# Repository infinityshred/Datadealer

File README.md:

# Datadealer
Datadealer synthesizer
Datadealer is a clone of Olivier Gillet's Shruthi-1 (https://github.com/pichenettes/shruthi-1). All boards in this repository are released under a cc-by-sa 3.0 license.

The firmware is released under a GPL3.0 license. It includes a
reimplementation of the formant synthesis algorithm used in Peter Knight's
Cantarino speech synthesizer.

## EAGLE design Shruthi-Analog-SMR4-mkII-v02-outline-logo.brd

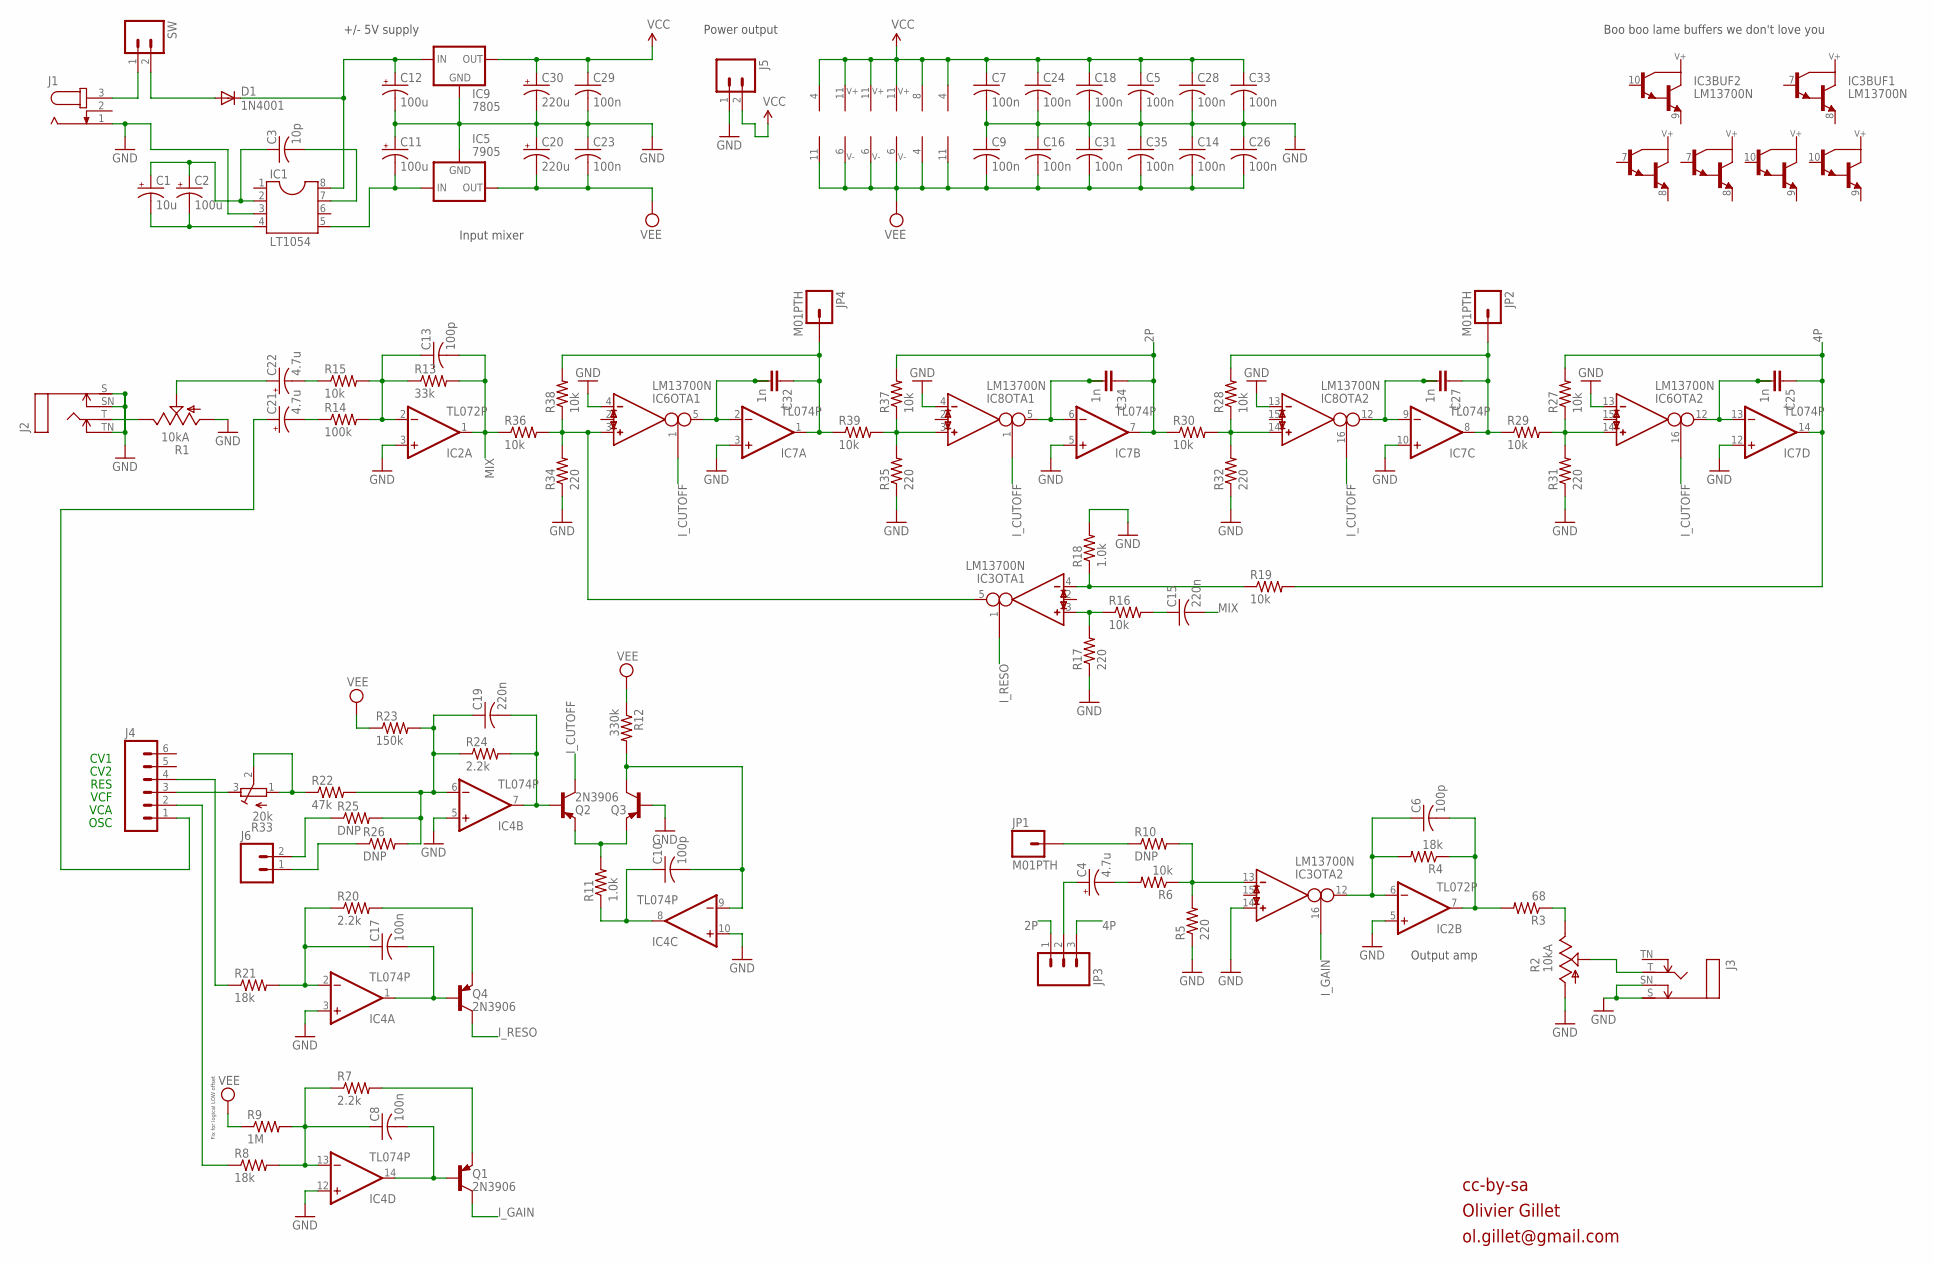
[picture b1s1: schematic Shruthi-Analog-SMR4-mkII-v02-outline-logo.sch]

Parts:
C1: 10u; E2,5-5
C2: 100u; E2,5-6
C3: 10p; C025-025X050
C4, C21, C22: 4.7u; E2,5-6
C5, C7, C8, C9, C14, C16, C17, C18, C23, C24, C26, C28, C29, C31, C33, C35: 100n; C025-025X050
C6, C10, C13: 100p; C025-025X050
C11, C12: 100u; E2,5-7
C15, C19: 220n; C025-025X050
C20, C30: 220u; E5-10,5
C25, C27, C32, C34: 1n; C2.5/5-2
D1: 1N4001; DO41-10
IC1: LT1054; DIL08
IC2: TL072P; DIL08
IC3, IC6, IC8: LM13700N; DIL16
IC4, IC7: TL074P; DIL14
IC5: 7905; 79XXS
IC9: 7805; 78XXS
J1: JACK-PLUG2; SPC4078_BIG_HOLES
J2, J3: MONOSWS; NMJ4HC-S
J4: M06SIP; 1X06
J5, J6: M02PTH; 1X02
JP1, JP2, JP4: M01PTH; 1X01
JP3: M03PTH; 1X03
Q1, Q2, Q3, Q4: 2N3906; TO92-
R1, R2: 10kA; CABLE_POT_6MM
R3: 68; 0204/7
R4, R8, R21: 18k; 0204/7
R5, R17, R31, R32, R34, R35: 220; 0204/7
R6, R15, R16, R19, R27, R28, R29, R30, R36, R37, R38, R39: 10k; 0204/7
R7, R20, R24: 2.2k; 0204/7
R9: 1M; 0204/7
R10, R25, R26: DNP; 0204V
R11, R18: 1.0k; 0204/7
R12: 330k; 0204/7
R13: 33k; 0204/7
R14: 100k; 0204/7
R22: 47k; 0204/7
R23: 150k; 0204/7
R33: 20k; RTRIM3296X
SW: M02PTH; 1X02

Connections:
2P: C34.1, IC7.7 (OUT), JP3.1, R30.1, R37.2
4P: C25.1, IC7.14 (OUT), JP3.3, R19.2, R27.2
GND: C5.2, C7.2, C9.1, C11.+, C12.-, C14.1, C16.1, C18.2, C20.+, C23.1, C24.2, C26.1, C28.2, C29.2, C30.-, C31.1, C33.2, C35.1, IC1.3, IC2.3 (+IN), IC2.5 (+IN), IC3.14 (IN_P), IC4.3 (+IN), IC4.5 (+IN), IC4.10 (+IN), IC4.12 (+IN), IC5.GND, IC6.4 (IN_N), IC6.13 (IN_N), IC7.3 (+IN), IC7.5 (+IN), IC7.10 (+IN), IC7.12 (+IN), IC8.4 (IN_N), IC8.13 (IN_N), IC9.GND, J1.1, J2.S, J2.SN, J2.TN, J3.S, J3.SN, J5.1, Q3.2 (B), R1.A, R2.A, R5.1, R17.1, R18.2, R31.1, R32.1, R34.1, R35.1
I_CUTOFF: IC6.1 (I_BIAS), IC6.16 (I_BIAS), IC8.1 (I_BIAS), IC8.16 (I_BIAS), Q2.1 (C)
I_GAIN: IC3.16 (I_BIAS), Q1.1 (C)
I_RESO: IC3.1 (I_BIAS), Q4.1 (C)
MIX: C13.2, C15.2, IC2.1 (OUT), R13.2, R36.1
unnamed: JP1.1, R10.1
unnamed: C19.2, IC4.7 (OUT), Q2.2 (B), R24.2
unnamed: R22.1, R33.1 (E), R33.2 (S)
unnamed: J4.3, R33.3 (A)
unnamed: C13.1, IC2.2 (-IN), R13.1, R14.2, R15.2
unnamed: Q2.3 (E), Q3.3 (E), R11.2
unnamed: C4.+, JP3.2
unnamed: C10.1, IC4.8 (OUT), R11.1
unnamed: C10.2, IC4.9 (-IN), Q3.1 (C), R12.2
unnamed: J4.4, R21.1
unnamed: IC3.5 (OUT), IC6.3 (IN_P), R34.2, R36.2, R38.1
unnamed: J3.T, R2.S
unnamed: C32.1, IC7.1 (OUT), JP4.1, R38.2, R39.1
unnamed: IC8.3 (IN_P), R35.2, R37.1, R39.2
unnamed: C4.-, R6.2
unnamed: J6.2, R25.1
unnamed: IC8.14 (IN_P), R28.1, R30.2, R32.2
unnamed: C15.1, R16.2
unnamed: J6.1, R26.1
unnamed: IC6.14 (IN_P), R27.1, R29.2, R31.2
unnamed: R2.E, R3.1
unnamed: C27.1, IC7.8 (OUT), JP2.1, R28.2, R29.1
unnamed: C32.2, C32.3, IC6.5 (OUT), IC7.2 (-IN)
unnamed: C34.2, C34.3, IC7.6 (-IN), IC8.5 (OUT)
unnamed: IC3.4 (IN_N), R18.1, R19.1
unnamed: C17.2, IC4.1 (OUT), Q4.2 (B)
unnamed: C8.2, IC4.14 (OUT), Q1.2 (B)
unnamed: IC3.3 (IN_P), R16.1, R17.2
unnamed: IC3.13 (IN_N), R5.2, R6.1, R10.2
unnamed: C21.+, J4.1
unnamed: C27.2, C27.3, IC7.9 (-IN), IC8.12 (OUT)
unnamed: C25.2, C25.3, IC6.12 (OUT), IC7.13 (-IN)
unnamed: J2.T, R1.E
unnamed: C21.-, R14.1
unnamed: C19.1, IC4.6 (-IN), R22.2, R23.2, R24.1, R25.2, R26.2
unnamed: J1.3, SW.1
unnamed: J4.2, R8.1
unnamed: C12.+, D1.C, IC1.8, IC9.IN
unnamed: C1.+, C2.+, C3.1, IC1.2
unnamed: C1.-, C2.-, IC1.4
unnamed: C3.2, IC1.7
unnamed: C8.1, IC4.13 (-IN), R7.1, R8.2, R9.2
unnamed: C17.1, IC4.2 (-IN), R20.1, R21.2
unnamed: C11.-, IC1.5, IC5.IN
unnamed: D1.A, SW.2
unnamed: Q4.3 (E), R20.2
unnamed: C6.2, IC2.7 (OUT), R3.2, R4.1
unnamed: C22.+, R1.S
unnamed: Q1.3 (E), R7.2
unnamed: C6.1, IC2.6 (-IN), IC3.12 (OUT), R4.2
unnamed: C22.-, R15.1
VCC: C5.1, C7.1, C18.1, C24.1, C28.1, C29.1, C30.+, C33.1, IC2.8 (V+), IC3.11 (V+), IC4.4 (V+), IC6.11 (V+), IC7.4 (V+), IC8.11 (V+), IC9.OUT, J5.2
VEE: C9.2, C14.2, C16.2, C20.-, C23.2, C26.2, C31.2, C35.2, IC2.4 (V-), IC3.6 (V-), IC4.11 (V-), IC5.OUT, IC6.6 (V-), IC7.11 (V-), IC8.6 (V-), R9.1, R12.1, R23.1

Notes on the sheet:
Power output
OSC
VCA
VCF
RES
cc-by-sa
Olivier Gillet
ol.gillet@gmail.com
Output amp
CV1
CV2
Input mixer
+/- 5V supply
Boo boo lame buffers we don't love you
Fix for logical LOW offset

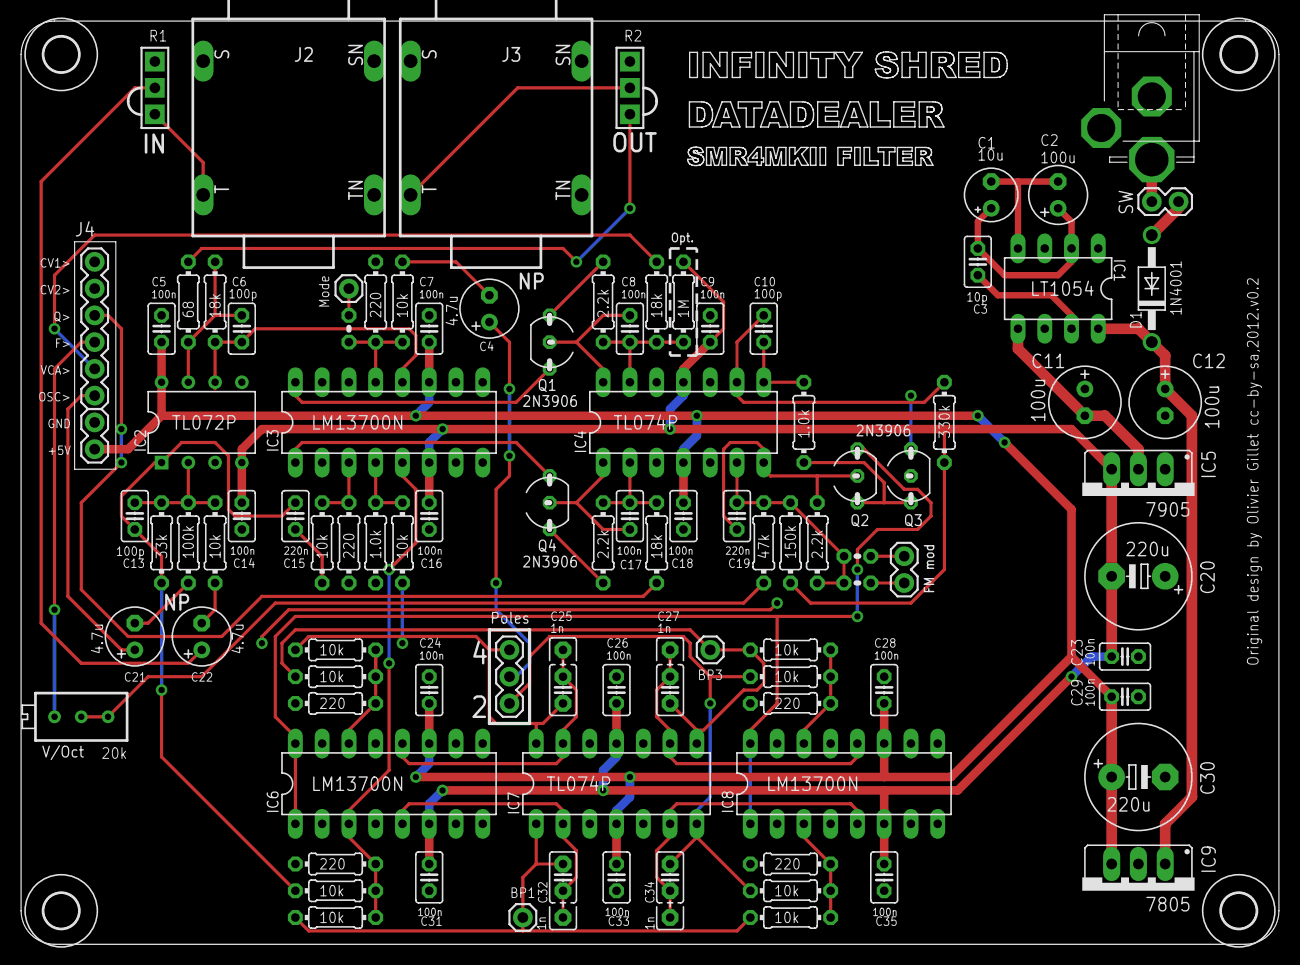
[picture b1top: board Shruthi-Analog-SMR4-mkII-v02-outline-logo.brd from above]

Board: 2 copper layers, 119.4 x 87.6 mm, 103 parts (0 on the bottom side), 60 nets.

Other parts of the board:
U$1, U$2, U$4, U$5: 3,3

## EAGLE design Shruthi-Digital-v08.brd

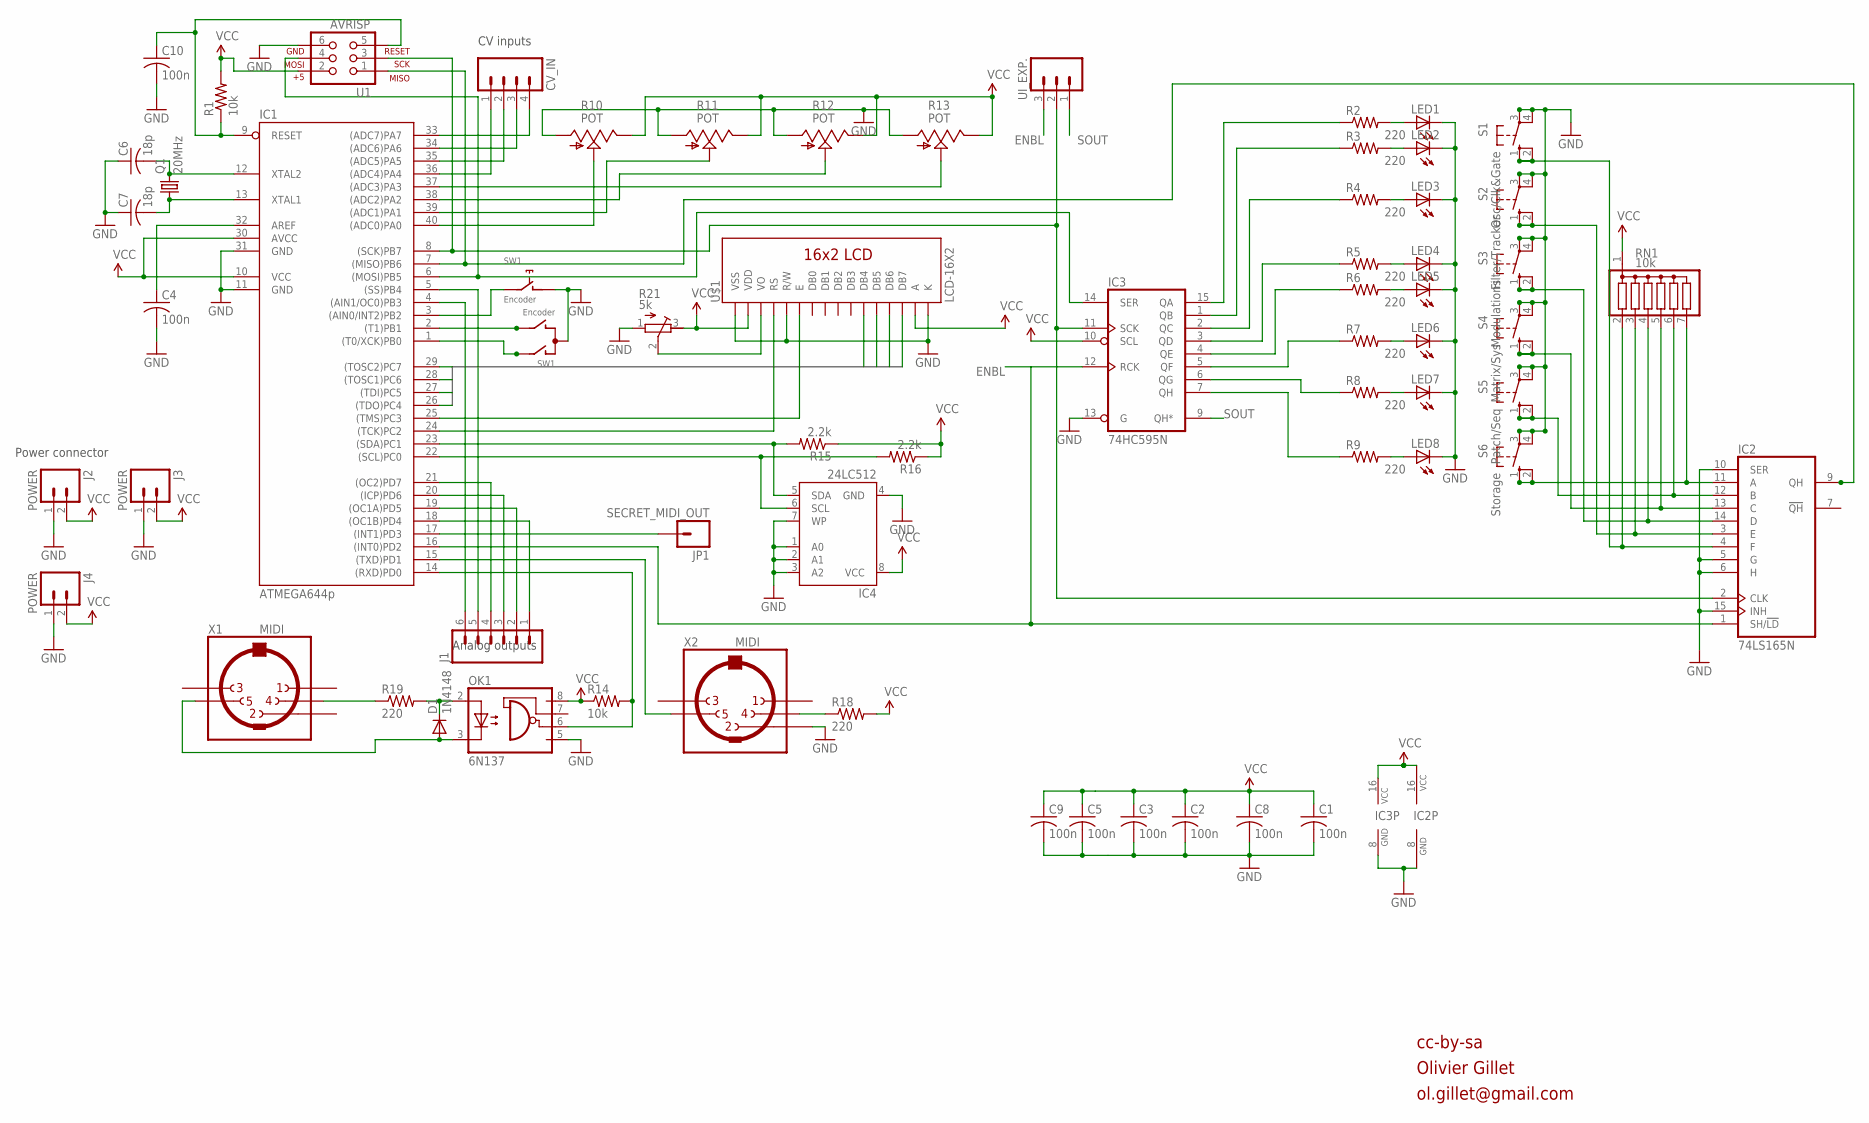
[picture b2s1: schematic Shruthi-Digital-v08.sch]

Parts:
C1, C2, C3, C4, C5, C8, C9, C10: 100n; C025-024X044
C6, C7: 18p; C025-024X044
CV_IN: M04PTH; 1X04
D1: 1N4148; D-5
IC1: ATMEGA644p; DIL40
IC2: 74LS165N; DIL16
IC3: 74HC595N; DIL16
IC4: 24LC512; DIL08
J1: M06SIP; 1X06
J2, J3, J4: POWER; 1X02
JP1: SECRET_MIDI_OUT; 1X01
LED1, LED2, LED3, LED4, LED5, LED6, LED7, LED8: LED3MM
OK1: 6N137; DIL08
Q1: 20MHz; HC49U-V
R1, R14: 10k; 0204/7
R2, R3, R4, R5, R6, R7, R8, R9, R18, R19: 220; 0204/7
R10, R11, R12, R13: POT; ALPS_POT_SFE
R15, R16: 2.2k; 0204/7
R21: 5k; RTRIM3296X
RN1: 10k; SIL7
S1: Osc/Clk&Gate; B3F-40XX
S2: Filter/Tracker; B3F-40XX
S3: Modulations; B3F-40XX
S4: Matrix/Sys; B3F-40XX
S5: Patch/Seq; B3F-40XX
S6: Storage; B3F-40XX
SW1: Encoder; ALPS_EC12E_SW
U1: AVRISP; 2X3
U$1: LCD-16X2
UI_EXP.: M03PTH; 1X03
X1, X2: MIDI; MAB5SH

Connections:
ENBL: IC1.16 ((INT0)PD2), IC2.1 (SH/!LD), IC3.12 (RCK), UI_EXP..3
GND: C1.2, C2.2, C3.2, C4.2, C5.2, C6.1, C7.1, C8.2, C9.2, C10.2, IC1.11 (GND), IC1.31 (GND), IC2.5 (G), IC2.6 (H), IC2.8 (GND), IC2.10 (SER), IC2.15 (INH), IC3.8 (GND), IC3.13 (G), IC4.1 (A0), IC4.2 (A1), IC4.3 (A2), IC4.4 (GND), IC4.7 (WP), J2.1, J3.1, J4.1, LED1.K (C), LED2.K (C), LED3.K (C), LED4.K (C), LED5.K (C), LED6.K (C), LED7.K (C), LED8.K (C), OK1.5 (GND), R10.P$3 (A), R11.P$3 (A), R12.P$3 (A), R13.P$3 (A), R21.1 (E), S1.3, S1.4 (P1), S2.3, S2.4 (P1), S3.3, S3.4 (P1), S4.3, S4.4 (P1), S5.3, S5.4 (P1), S6.3, S6.4 (P1), SW1.C, SW1.D (1), U1.6, U$1.1 (VSS), U$1.5 (R/W), U$1.16 (K), X2.2
LCD_DATA1: IC1.26 ((TDO)PC4), U$1.11 (DB4)
LCD_DATA2: IC1.27 ((TDI)PC5), U$1.12 (DB5)
LCD_DATA3: IC1.28 ((TOSC1)PC6), U$1.13 (DB6)
LCD_DATA4: IC1.29 ((TOSC2)PC7), U$1.14 (DB7)
unnamed: IC3.2 (QC), R4.1
unnamed: IC1.24 ((TCK)PC2), U$1.4 (RS)
unnamed: IC2.11 (A), RN1.7, S6.1 (S), S6.2 (S1)
unnamed: IC2.3 (E), RN1.3, S2.1 (S), S2.2 (S1)
unnamed: C10.1, IC1.9 (RESET), R1.1, U1.5
unnamed: C4.1, IC1.32 (AREF)
unnamed: IC1.8 ((SCK)PB7), IC2.2 (CLK), IC3.11 (SCK), U1.3, UI_EXP..2
unnamed: IC1.7 ((MISO)PB6), IC2.9 (QH), U1.1
unnamed: CV_IN.1, IC1.36 ((ADC4)PA4)
unnamed: CV_IN.2, IC1.35 ((ADC5)PA5)
unnamed: CV_IN.3, IC1.34 ((ADC6)PA6)
unnamed: CV_IN.4, IC1.33 ((ADC7)PA7)
unnamed: IC1.40 ((ADC0)PA0), R10.P$2 (S)
unnamed: IC1.39 ((ADC1)PA1), R11.P$2 (S)
unnamed: IC1.38 ((ADC2)PA2), R12.P$2 (S)
unnamed: IC1.37 ((ADC3)PA3), R13.P$2 (S)
unnamed: IC1.4 ((AIN1/OC0)PB3), J1.6
unnamed: IC1.5 ((SS)PB4), J1.5
unnamed: IC1.18 ((OC1B)PD4), J1.1
unnamed: IC1.19 ((OC1A)PD5), J1.2
unnamed: IC1.20 ((ICP)PD6), J1.3
unnamed: IC1.21 ((OC2)PD7), J1.4
unnamed: IC1.17 ((INT1)PD3), JP1.1
unnamed: IC1.23 ((SDA)PC1), IC4.5 (SDA), R15.2
unnamed: D1.C, OK1.2 (A), R19.2
unnamed: IC3.15 (QA), R2.1
unnamed: IC3.1 (QB), R3.1
unnamed: IC1.22 ((SCL)PC0), IC4.6 (SCL), R16.2
unnamed: IC3.3 (QD), R5.1
unnamed: IC3.4 (QE), R6.1
unnamed: IC3.5 (QF), R7.1
unnamed: IC3.7 (QH), R9.1
unnamed: IC3.6 (QG), R8.1
unnamed: LED1.A, R2.2
unnamed: LED2.A, R3.2
unnamed: LED3.A, R4.2
unnamed: LED4.A, R5.2
unnamed: LED5.A, R6.2
unnamed: LED6.A, R7.2
unnamed: LED7.A, R8.2
unnamed: LED8.A, R9.2
unnamed: IC1.6 ((MOSI)PB5), IC3.14 (SER), U1.4
unnamed: IC2.4 (F), RN1.2, S1.1 (S), S1.2 (S1)
unnamed: IC2.14 (D), RN1.4, S3.1 (S), S3.2 (S1)
unnamed: IC2.13 (C), RN1.5, S4.1 (S), S4.2 (S1)
unnamed: IC2.12 (B), RN1.6, S5.1 (S), S5.2 (S1)
unnamed: IC1.1 ((T0/XCK)PB0), SW1.A
unnamed: IC1.2 ((T1)PB1), SW1.B
unnamed: IC1.3 ((AIN0/INT2)PB2), SW1.E (2)
unnamed: R18.1, X2.4
unnamed: IC1.15 ((TXD)PD1), X2.5
unnamed: IC1.14 ((RXD)PD0), OK1.6 (VO), R14.2
unnamed: R19.1, X1.4
unnamed: D1.A, OK1.3 (C), X1.5
unnamed: IC1.25 ((TMS)PC3), U$1.6 (E)
unnamed: R21.2 (S), U$1.3 (VO)
unnamed: C7.2, IC1.13 (XTAL1), Q1.1
unnamed: C6.2, IC1.12 (XTAL2), Q1.2
SOUT: IC3.9 (QH*), UI_EXP..1
VCC: C1.1, C2.1, C3.1, C5.1, C8.1, C9.1, IC1.10 (VCC), IC1.30 (AVCC), IC2.16 (VCC), IC3.10 (SCL), IC3.16 (VCC), IC4.8 (VCC), J2.2, J3.2, J4.2, OK1.8 (VCC), R1.2, R10.P$1 (E), R11.P$1 (E), R12.P$1 (E), R13.P$1 (E), R14.1, R15.1, R16.1, R18.2, R21.3 (A), RN1.1, U1.2, U$1.2 (VDD), U$1.15 (A)

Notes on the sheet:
CV inputs
Power connector
Analog outputs
cc-by-sa
Olivier Gillet
ol.gillet@gmail.com

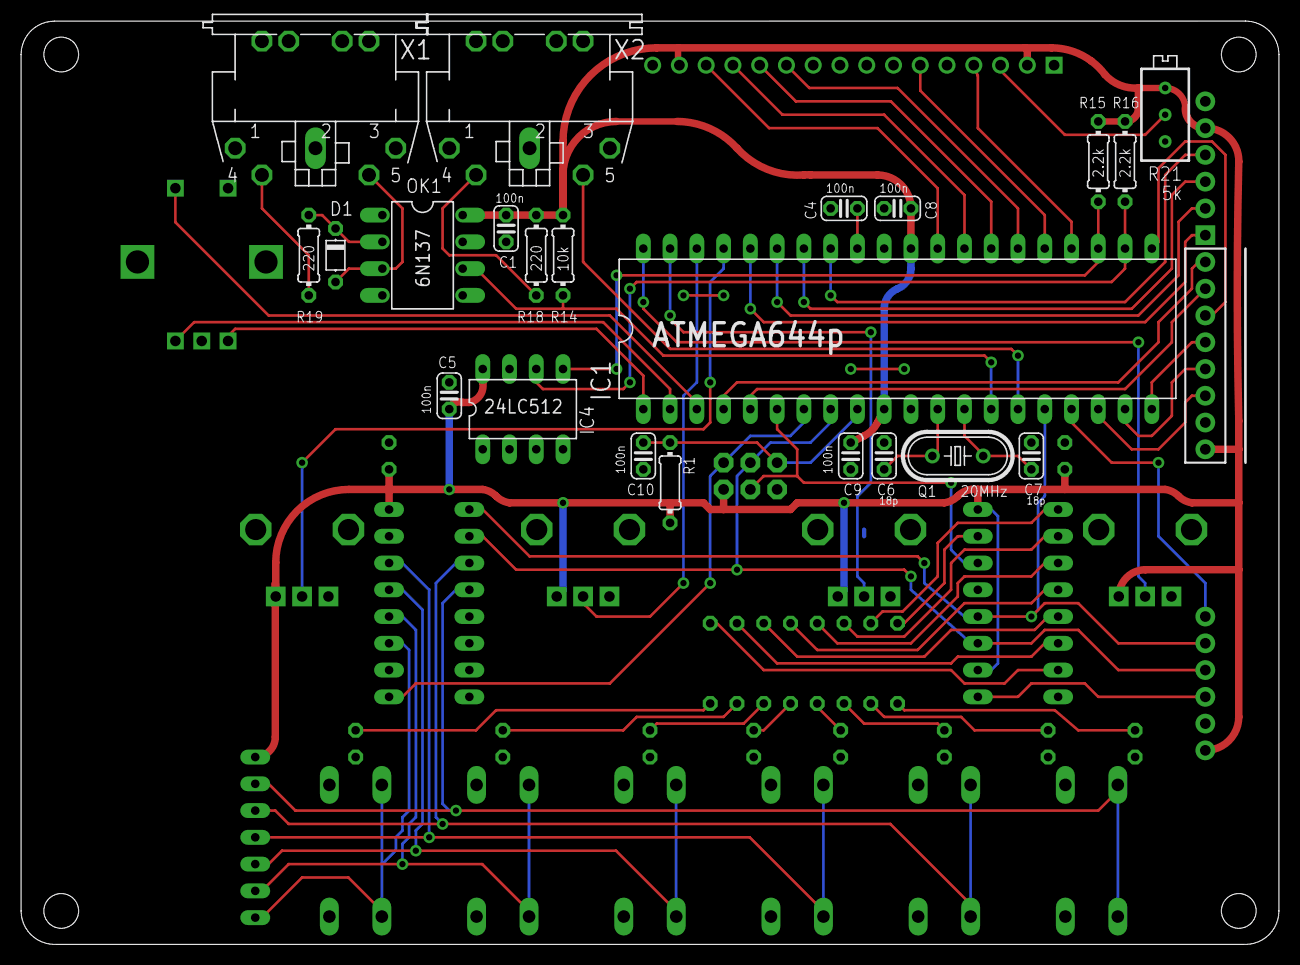
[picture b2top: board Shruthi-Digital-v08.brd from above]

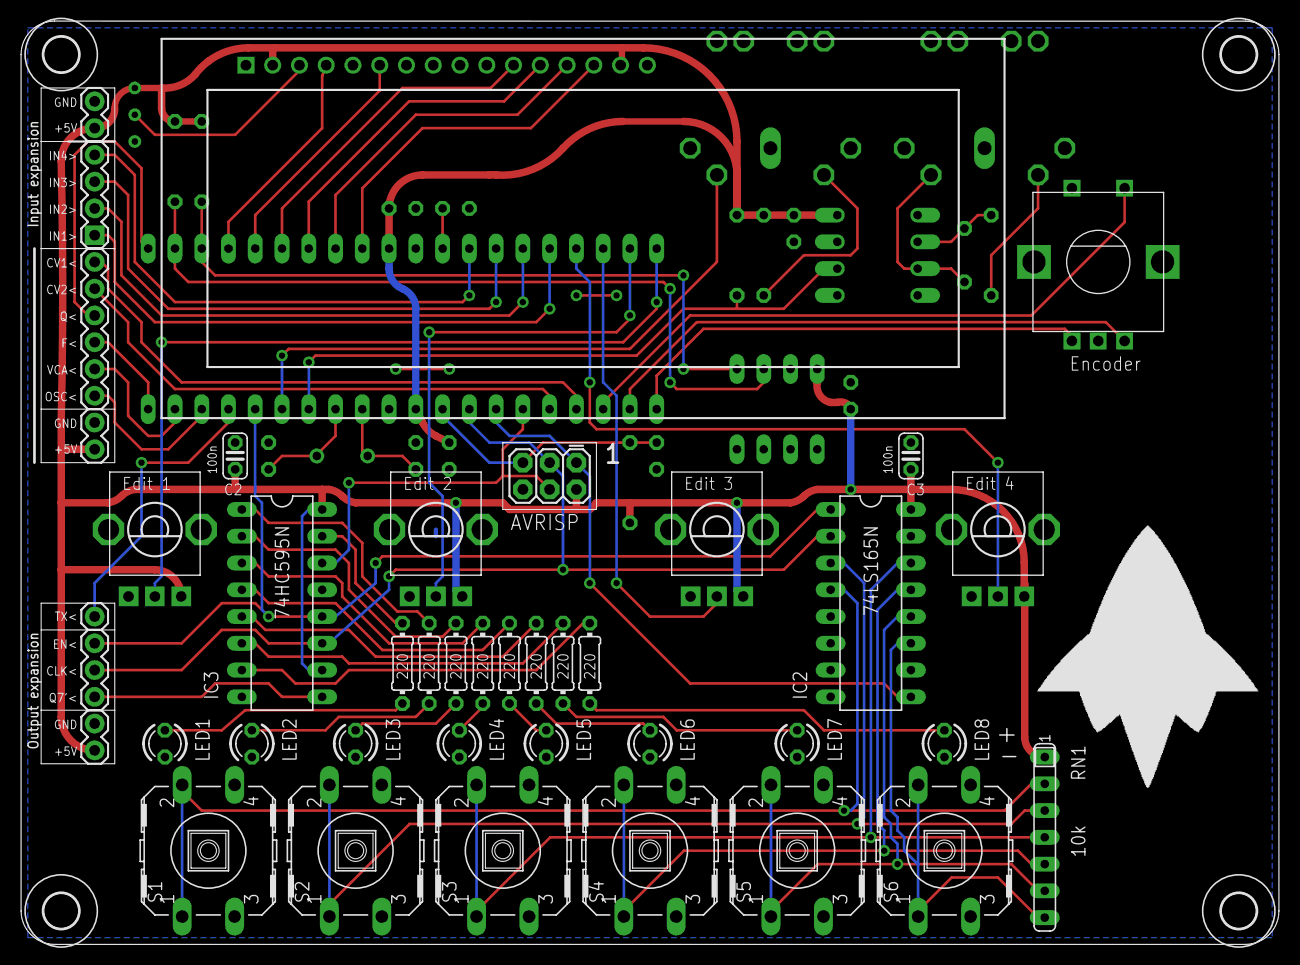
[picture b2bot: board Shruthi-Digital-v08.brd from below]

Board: 2 copper layers, 119.4 x 87.6 mm, 67 parts (45 on the bottom side), 66 nets.

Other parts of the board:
U$2, U$3, U$4, U$5: 3,3

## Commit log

2016-10-07 Deleted old firmware

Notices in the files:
Shruthi-Analog-SMR4-mkII-v02-outline-logo.brd:
Original design by Olivier Gillet cc-by-sa,2012.v0.2
